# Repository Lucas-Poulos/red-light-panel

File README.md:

# red-light-panel

A battery-powered 660nm red light therapy panel. 4S2P 18650 Li-ion pack
(~74Wh-class), USB-C PD charging, ~74W LED load across two independently
PWM-dimmable channels, STM32-based control with a 4-button HMI.

KiCad 10 hardware project — schematic + BOM. PCB placement/routing is
out of scope for this pass, but the board is fab-ready to route against:
2-layer, 1oz/1oz copper, JLCPCB-standard-service design rules with
margin (not run at the fabrication limit) — see
`docs/pcb_fabrication_rules.md` for the exact values and rationale.
All 153 components are imported onto the board from the schematic.

## Architecture

Seven hierarchical sheets, numbered so KiCad's hierarchy navigator sorts
them in build/reading order:

| Sheet | Description |
|---|---|
| `01_battery_protection` | 4S2P 18650 pack, BQ76920 protection AFE, high-side dual-FET protection, reverse-polarity guard |
| `02_usbc_charging` | USB-C PD input (TPS25751), buck-boost charger (BQ25792), ESD protection |
| `03_power_rail_3v3` | TPS563201 buck regulator, 3.3V system logic rail |
| `04_led_drivers` | 2x LM3409HV PFET-buck constant-current LED driver channels |
| `05_led_array` | 64x Luminus SST-10-DR-B130-K660 660nm LEDs, 2 channels x 8 parallel x 4 series strings |
| `06_mcu_control` | STM32G031K8T6 MCU, SWD debug (Cortex Debug 10-pin + THT breakout), ESD arrays |
| `07_hmi` | 4 tactile buttons (power/dim+/dim-/mode), single-color status LED |

Connectivity uses `GlobalLabel`s throughout rather than wired
hierarchical sheet-symbol pins — see `docs/design_notes.md` for why. The
root sheet (`red-light-panel.kicad_sch`) contains only the 7 sheet
symbols, no components.

## Opening the project

Requires **KiCad 10**. Clone the repo and open `red-light-panel.kicad_pro`
— the project-local `sym-lib-table`/`fp-lib-table` register every stock
library this design uses (via `${KICAD10_SYMBOL_DIR}`/
`${KICAD10_FOOTPRINT_DIR}`, so they resolve on any machine with KiCad 10
installed) plus `libs/red-light-panel.kicad_sym` / `.pretty` for the
handful of parts not in KiCad's stock libraries. No global library setup
is required.

## Regenerating the schematics

The 7 sub-sheets and the root sheet are generated programmatically from
`tools/kicad_gen/` (a small `kiutils`-based builder), not hand-drawn —
see `docs/design_notes.md` "Schematic generation approach" for the full
pipeline and the non-obvious KiCad file-format details it works around.
To rebuild everything from the declarative part lists in
`tools/kicad_gen/sheet*.py`:

```
pip install kiutils sexpdata
python3 tools/kicad_gen/sheet1.py   # ... through sheet7.py
python3 tools/kicad_gen/root_sheet.py
python3 tools/kicad_gen/fix_instance_paths.py
```

## Regenerating the BOM

```
python3 bom/generate_bom.py
```

Wraps `kicad-cli sch export bom` (reads the full hierarchical netlist
including the custom `MPN`/`Manufacturer`/`DigiKey_PN`/`Sheet` fields set
on every symbol) grouped by `(MPN, Value, Footprint)` into
`bom/red-light-panel-bom.csv` — 48 rows, 153 total placed components.

## Current design status

**Verification**: full-hierarchy `kicad-cli sch erc` on
`red-light-panel.kicad_sch` reports **0 errors** (157 cosmetic
"endpoint off grid" warnings from the auto-placed layout, 3 expected
"lib_symbol_mismatch" warnings from stock parts whose KiCad-library
`extends` chain was flattened for pin-position reliability — see
`docs/design_notes.md`). Every one of the 153 placed components has a
linked footprint; zero duplicate reference designators.

### Known open items (flagged, need your review before fab)

**Corrections to the original BOM** (verified real part numbers/topology
fixes, not silent substitutions to different components):
- `TPD4S012DBVR` → **TPD4S012DRYR** (that BVR suffix/package doesn't
  exist for this part; TI only makes it in a 6-pin USON).
- `TPD4E001DZDR` → **TPD4E001DBVR** (same issue; the 4-channel device
  needs a 6-pin SOT-23, not the 4-pin DZD package).
- `TPS25750DRYR` → **TPS25751DREFR** (TPS25750 is TI-marked
  Not-Recommended-for-New-Designs; TPS25751 is the active replacement —
  your decision, see below).
- Fuse `MICROSMD250F/16-2` (originally a placeholder) → **Bel Fuse
  0ZRE0025FF** (0.25A hold current, matching the placeholder's own naming
  convention) — verify hold-current spec against your real current
  budget before finalizing.
- Status LED `APTD1608LSECK/J4-PRV` → confirmed **single-color**
  (`APT1608LSECK/J4-PRV`, no "D") — no real bi-color part exists under
  that family name. Per your decision, D71 (renumbered from D8, see
  below) is now a single-color status LED.
- Reference designators **D6/D7/D8 renumbered to D69/D70/D71**: the
  original BOM's own `D5-D68` (64 LED array elements) numerically
  collided with these three (sheet 6 ESD arrays, sheet 7 status LED).

**Needs your engineering review** (reasonable, documented, but
unverified-against-datasheet or genuinely open decisions):
- **BQ25792's front-end ideal-diode MOSFETs (ACFET/RBFET1/RBFET2) are not
  included** — TI's real reference design needs them on the
  ACDRV1/ACDRV2/BTST1/BTST2 pins, but they weren't itemized in the
  original BOM and weren't invented here unprompted. The charger's
  reverse-blocking front-end is incomplete as generated until you decide
  whether/how to add this.
- **TPS25751DREFR and BQ25792RQMR are hand-built symbols** (no official
  downloadable KiCad source exists for either — confirmed via TI/DigiKey/
  Ultra Librarian). Every pin was sourced from TI's own datasheet pin
  tables, but several individual pins have ambiguous datasheet electrical
  types (TI itself labels some pins as generic "P"/"I/O") — double-check
  before trusting blind, especially: TPS25751's `LDO_1V5`/`DRAIN`/`PPHV`/
  `VBUS_IN`; BQ25792's `BTST1`/`BTST2`/`VAC1`/`VAC2`/`BATP`/`BAT`/`PMID`.
- **TPS25751's power-path topology** (VBUS_IN → internal switch →
  PPHV/DRAIN → BQ25792) is a best-effort interpretation of TI's own
  ambiguous datasheet, not confirmed against a real TI reference design.
- **LED array topology** (8 parallel strings of 4 series LEDs per
  channel, ~625mA/string) is derived from Vf/rail-voltage math, not
  specified by the BOM — verify against the ~74W target power budget and
  the Luminus datasheet's thermal-derating curves.
- **STM32G031 GPIO assignment** (I2C on PB6/PB7, PWM on PA6/PA7, buttons
  on PA0-PA3, NTC ADC on PA4, NRST on PF2) is a reasonable but
  **unverified-against-the-reference-manual** pin choice.
- **Driver inductors** (L2/L3, Vishay IHLP2525CZERR10M01) and the 3.3V
  rail inductor (L1, Wurth 744031220) — values need a real switching-
  frequency calc against LM3409HV's/TPS563201's design equations, not
  just the default values used here.
- **L1's footprint** is a size-matched placeholder (no exact Wurth
  744031220 footprint exists in KiCad's stock libraries).
- **J3's exact GCT USB4105 suffix** (plating/stake length) — defaulted
  to `USB4105-GF-A`; there is no "mount style" suffix (confirmed via
  research — the whole series is one fixed SMT top-mount style).
- **J6's footprint** (generic 2x5 1.27mm SMD header) is electrically
  equivalent to but not the exact Samtec FTSH-105-01-F-DV-K footprint.
- **Calculated component values** flagged inline in their `Value` field
  wherever a real datasheet equation was used instead of an itemized BOM
  value: R3 (3.3V feedback divider bottom leg), R13 (status LED current
  limit), and every "(added, flagged)" support passive (COFF/UVLO
  networks, bootstrap caps, ILIM_HIZ/PROG set resistors, NTC pull-up) —
  see `tools/kicad_gen/sheet*.py` docstrings for the reasoning behind
  each.

None of the above are unresolved *nets* or missing pin connections —
every flagged item is a component-value/part-choice judgment call called
out for your review, consistent with a 0-error ERC pass.

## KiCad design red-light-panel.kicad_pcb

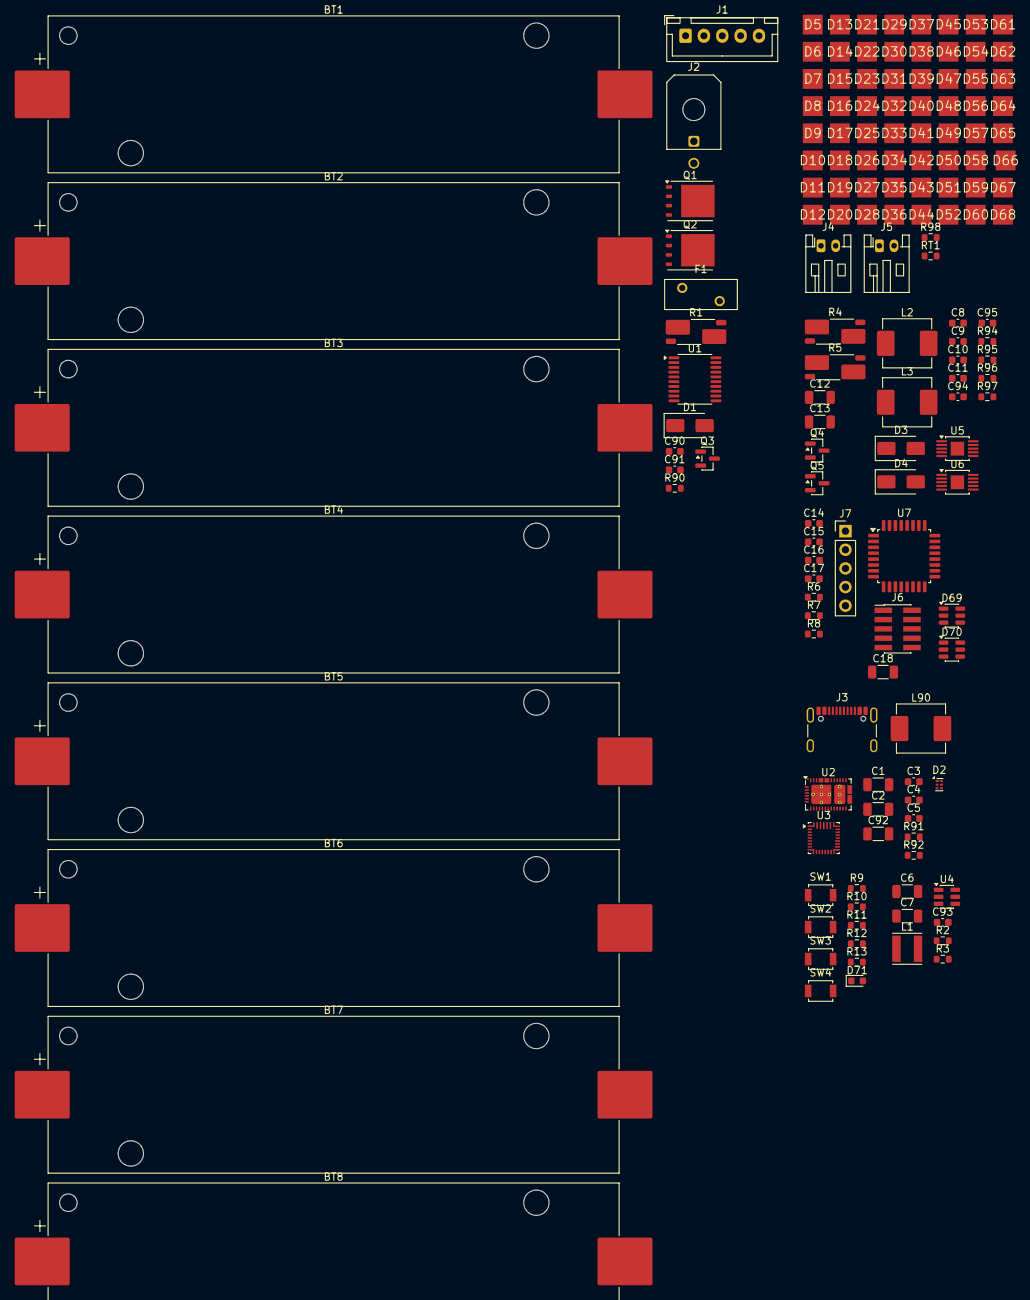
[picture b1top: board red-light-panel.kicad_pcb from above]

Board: 2 copper layers, 153 parts (0 on the bottom side), 98 nets, no tracks yet.

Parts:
BT1, BT2, BT3, BT4, BT5, BT6, BT7, BT8: INR18650-30Q; BatteryHolder_Keystone_1042_1x18650
C1, C2, C6, C7, C12, C13: 10uF; C_1206_3216Metric
C3, C4, C5, C8, C9, C10, C11, C14, C15, C16, C17: 0.1uF; C_0603_1608Metric
C18: 4.7uF; C_1206_3216Metric
C90: 1uF (added, flagged); C_0603_1608Metric
C91: 0.1uF (added, flagged); C_0603_1608Metric
C92: 1uF (added, flagged -- PMID bulk cap per typical 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; C_1206_3216Metric
C93: 2.2nF (added, flagged -- VBST bootstrap cap); C_0603_1608Metric
C94, C95: 100pF (added, flagged -- COFF timing, calc vs L f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; C_0603_1608Metric
D1: SMAJ24CA; D_SMA
D2: TPD4S012DRYR (corrected from BOM's TPD4S012DBVR -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; Texas_USON-6_1x1.45mm_P0.5mm_SMD
D3, D4: SS54; D_SMA
D5, D6, D7, D8, D9, D10, D11, D12, D13, D14, D15, D16, D17, D18, D19, D20, D21, D22, D23, D24, D25, D26, D27, D28, D29, D30, D31, D32, D33, D34, D35, D36, D37, D38, D39, D40, D41, D42, D43, D44, D45, D46, D47, D48, D49, D50, D51, D52, D53, D54, D55, D56, D57, D58, D59, D60, D61, D62, D63, D64, D65, D66, D67, D68: SST-10-DR-B130-K660; LUMINUS_SST-10-3535
D69, D70: TPD4E001DBVR (corrected from BOM's TPD4E001DZDR -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; SOT-23-6
D71: APT1608LSECK/J4-PRV (single-color, corrected per 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; LED_0603_1608Metric
F1: 0.25A resettable; Fuse_BelFuse_0ZRE0025FF_L9.6mm_W3.8mm
J1: JST B5B-XH-A; JST_XH_B5B-XH-A_1x05_P2.50mm_Vertical
J2: Molex 43045-0200; Molex_Micro-Fit_3.0_43045-0200_2x01_P3.00mm_Horizontal
J3: USB4105-GF-A (plating/stake length TBD, flag); USB_C_Receptacle_GCT_USB4105-xx-A_16P_TopMnt_Horizontal
J4, J5: 2-pin screw terminal / JST-PH-2; JST_PH_S2B-PH-K_1x02_P2.00mm_Horizontal
J6: Cortex Debug 10-pin; PinHeader_2x05_P1.27mm_Vertical_SMD
J7: Debug breakout (SWDIO,SWCLK,NRST,3.3V,GND); PinHeader_1x05_P2.54mm_Vertical
L1: 2.2uH (Wurth 744031220); L_Vishay_IFSC-1515AH_4x4x1.8mm
L2, L3: IHLP2525CZERR10M01 (0.10uH); L_Vishay_IHLP-2525
L90: 2.2uH (added, flagged -- calc vs target charge cu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; L_Vishay_IHLP-2525
Q1, Q2: CSD18540Q5B; TDSON-8-1
Q3: AO3401A; SOT-23
Q4, Q5: AO3401A (30V Vds, satisfies brief's margin flag); SOT-23
R1: 0.01R 1%; R_Shunt_Vishay_WSK2512_6332Metric_T2.21mm
R2, R6, R7, R8, R9, R10, R11, R12: 10k; R_0603_1608Metric
R3: 3.01k (calc, flag); R_0603_1608Metric
R4, R5: 0.02R 1%; R_Shunt_Vishay_WSK2512_6332Metric_T2.21mm
R13: 680R (calc vs Vf/If, flag); R_0603_1608Metric
R90: 100k; R_0603_1608Metric
R91: 10k (added, flagged -- ILIM_HIZ set resistor, cal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; R_0603_1608Metric
R92: 4.7k (added, flagged -- PROG set resistor, calc p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; R_0603_1608Metric
R94, R96: 100k (added, flagged -- COFF timing, calc vs L fr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; R_0603_1608Metric
R95, R97: 100k (added, flagged -- UVLO always-on pull-up, n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; R_0603_1608Metric
R98: 10k (added, flagged -- NTC divider pull-up); R_0603_1608Metric
RT1: NCP18XH103F03RB (10k NTC); R_0603_1608Metric
SW1, SW2, SW3, SW4: Omron B3U-1000P; SW_SPST_B3U-1000P
U1: BQ76920PW; TSSOP-20_4.4x6.5mm_P0.65mm
U2: TPS25751DREFR (active replacement for NRND TPS257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; Texas_REF0038A_WQFN-38-2EP_6x4mm_P0.4
U3: BQ25792RQMR; Texas_RQM0029A_VQFN-29_4x4mm_P0.4mm
U4: TPS563201DDCR; SOT-23-6
U5, U6: LM3409HVMY/NOPB; HVSSOP-10-1EP_3x3mm_P0.5mm_EP1.83x1.89mm
U7: STM32G031K8T6; LQFP-32_7x7mm_P0.8mm

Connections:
3V3: C7.1, C14.1, C15.1, C16.1, C17.1, C18.1, D69.6 (VCC), D70.6 (VCC), J6.1 (VTref), J7.4, L1.2, R2.1, R6.1, R7.1, R8.1, R13.1, R98.1, SW1.1, SW2.1, SW3.1, SW4.1, U7.4 (VDD)
BTN_DIMM: D69.4 (IO3), R11.1, SW3.2, U7.9 (PA2)
BTN_DIMP: D69.3 (IO2), R10.1, SW2.2, U7.8 (PA1)
BTN_MODE: D69.5 (IO4), R12.1, SW4.2, U7.10 (PA3)
BTN_PWR: D69.1 (IO1), R9.1, SW1.2, U7.7 (PA0)
D8_A: D71.2 (A), R13.2
FET_MID: Q1.1 (S), Q1.2 (S), Q1.3 (S), Q2.1 (S), Q2.2 (S), Q2.3 (S)
GND: C1.2, C2.2, C3.2, C4.2, C5.2, C6.2, C7.2, C8.2, C9.2, C10.2, C11.2, C14.2, C15.2, C16.2, C17.2, C18.2, C90.2, C91.2, C92.2, C94.2, C95.2, D1.2 (A2), D2.4 (GND), D3.2 (A), D4.2 (A), D69.2 (GND), D70.2 (GND), J3.A1 (GND), J3.A12 (GND), J3.B1 (GND), J3.B12 (GND), J3.SH (SHIELD), J6.3 (GND), J6.5 (GND), J6.9 (GNDDetect), J7.5, R1.2, R3.2, R9.2, R10.2, R11.2, R12.2, R91.2, R92.2, RT1.2, U4.1 (GND), U5.5 (GND), U5.11 (DAP), U6.5 (GND), U6.11 (DAP), U7.5 (VSS)
I2C_SCL: R7.2, U7.30 (PB6)
I2C_SDA: R6.2, U7.31 (PB7)
LED_A+: C12.1, D5.2 (A), D9.2 (A), D13.2 (A), D17.2 (A), D21.2 (A), D25.2 (A), D29.2 (A), D33.2 (A), J4.1, L2.2
LED_A-: C12.2, D8.1 (K), D12.1 (K), D16.1 (K), D20.1 (K), D24.1 (K), D28.1 (K), D32.1 (K), D36.1 (K), J4.2, R4.1, U5.8 (CSP)
LED_A_S0_N0: D5.1 (K), D6.2 (A)
LED_A_S0_N1: D6.1 (K), D7.2 (A)
LED_A_S0_N2: D7.1 (K), D8.2 (A)
LED_A_S1_N0: D9.1 (K), D10.2 (A)
LED_A_S1_N1: D10.1 (K), D11.2 (A)
LED_A_S1_N2: D11.1 (K), D12.2 (A)
LED_A_S2_N0: D13.1 (K), D14.2 (A)
LED_A_S2_N1: D14.1 (K), D15.2 (A)
LED_A_S2_N2: D15.1 (K), D16.2 (A)
LED_A_S3_N0: D17.1 (K), D18.2 (A)
LED_A_S3_N1: D18.1 (K), D19.2 (A)
LED_A_S3_N2: D19.1 (K), D20.2 (A)
LED_A_S4_N0: D21.1 (K), D22.2 (A)
LED_A_S4_N1: D22.1 (K), D23.2 (A)
LED_A_S4_N2: D23.1 (K), D24.2 (A)
LED_A_S5_N0: D25.1 (K), D26.2 (A)
LED_A_S5_N1: D26.1 (K), D27.2 (A)
LED_A_S5_N2: D27.1 (K), D28.2 (A)
LED_A_S6_N0: D29.1 (K), D30.2 (A)
LED_A_S6_N1: D30.1 (K), D31.2 (A)
LED_A_S6_N2: D31.1 (K), D32.2 (A)
LED_A_S7_N0: D33.1 (K), D34.2 (A)
LED_A_S7_N1: D34.1 (K), D35.2 (A)
LED_A_S7_N2: D35.1 (K), D36.2 (A)
LED_B+: C13.1, D37.2 (A), D41.2 (A), D45.2 (A), D49.2 (A), D53.2 (A), D57.2 (A), D61.2 (A), D65.2 (A), J5.1, L3.2
LED_B-: C13.2, D40.1 (K), D44.1 (K), D48.1 (K), D52.1 (K), D56.1 (K), D60.1 (K), D64.1 (K), D68.1 (K), J5.2, R5.1, U6.8 (CSP)
LED_B_S0_N0: D37.1 (K), D38.2 (A)
LED_B_S0_N1: D38.1 (K), D39.2 (A)
LED_B_S0_N2: D39.1 (K), D40.2 (A)
LED_B_S1_N0: D41.1 (K), D42.2 (A)
LED_B_S1_N1: D42.1 (K), D43.2 (A)
LED_B_S1_N2: D43.1 (K), D44.2 (A)
LED_B_S2_N0: D45.1 (K), D46.2 (A)
LED_B_S2_N1: D46.1 (K), D47.2 (A)
LED_B_S2_N2: D47.1 (K), D48.2 (A)
LED_B_S3_N0: D49.1 (K), D50.2 (A)
LED_B_S3_N1: D50.1 (K), D51.2 (A)
LED_B_S3_N2: D51.1 (K), D52.2 (A)
LED_B_S4_N0: D53.1 (K), D54.2 (A)
LED_B_S4_N1: D54.1 (K), D55.2 (A)
LED_B_S4_N2: D55.1 (K), D56.2 (A)
LED_B_S5_N0: D57.1 (K), D58.2 (A)
LED_B_S5_N1: D58.1 (K), D59.2 (A)
LED_B_S5_N2: D59.1 (K), D60.2 (A)
LED_B_S6_N0: D61.1 (K), D62.2 (A)
LED_B_S6_N1: D62.1 (K), D63.2 (A)
LED_B_S6_N2: D63.1 (K), D64.2 (A)
LED_B_S7_N0: D65.1 (K), D66.2 (A)
LED_B_S7_N1: D66.1 (K), D67.2 (A)
LED_B_S7_N2: D67.1 (K), D68.2 (A)
NRST: D70.4 (IO3), J6.10 (~RESET), J7.3, R8.2, U7.6 (PF2)
NTC_SENSE: R98.2, RT1.1, U7.11 (PA4)
unnamed: BT1.1 (+), BT3.2 (-)
unnamed: BT2.1 (+), BT4.2 (-)
unnamed: BT3.1 (+), BT5.2 (-)
unnamed: BT4.1 (+), BT6.2 (-)
unnamed: BT5.1 (+), BT7.2 (-)
unnamed: BT6.1 (+), BT8.2 (-)
PACK_RAW: F1.2, Q3.2 (S)
PACK_RAW_F: F1.1, J2.1
PWM_A: U5.3 (EN), U7.13 (PA6)
PWM_B: U6.3 (EN), U7.14 (PA7)
Q3_GATE: Q3.1 (G), R90.1
STACK_NEG: BT1.2 (-), BT2.2 (-), J1.1, J2.2, R1.1
SWCLK: D70.3 (IO2), J6.4 (SWCLK/TCK), J7.2, U7.25 (PA14)
SWDIO: D70.1 (IO1), J6.2 (SWDIO/TMS), J7.1, U7.24 (PA13)
U4_FB: R2.2, R3.1, U4.4 (VFB)
U4_SW: C93.2, L1.1, U4.2 (SW)
U4_VBST: C93.1, U4.6 (VBST)
U5_COFF: C94.1, R94.2, U5.4 (COFF)
U5_CSN: R4.2, U5.7 (CSN)
U5_PGATE: Q4.1 (G), U5.6 (PGATE)
U5_SW: D3.1 (K), L2.1, Q4.3 (D)
U5_UVLO: R95.2, U5.1 (UVLO)
U5_VCC: C8.1, C9.1, U5.2 (IADJ), U5.9 (VCC)
U6_COFF: C95.1, R96.2, U6.4 (COFF)
U6_CSN: R5.2, U6.7 (CSN)
U6_PGATE: Q5.1 (G), U6.6 (PGATE)
U6_SW: D4.1 (K), L3.1, Q5.3 (D)
U6_UVLO: R97.2, U6.1 (UVLO)
U6_VCC: C10.1, C11.1, U6.2 (IADJ), U6.9 (VCC)
USB_DN: D2.2 (D-), J3.A7 (D-), J3.B7 (D-)
USB_DP: D2.1 (D+), J3.A6 (D+), J3.B6 (D+)
USB_VBUS: C1.1, C2.1, D2.6 (VBUS), J3.A4 (VBUS), J3.A9 (VBUS), J3.B4 (VBUS), J3.B9 (VBUS)
VBAT: BT7.1 (+), BT8.1 (+), C6.1, D1.1 (A1), J1.5, Q1.5 (D), Q3.3 (D), R90.2, U4.3 (VIN), U4.5 (EN)
VBAT_PROT: Q2.5 (D), Q4.2 (S), Q5.2 (S), R94.1, R95.1, R96.1, R97.1, U5.10 (VIN), U6.10 (VIN)

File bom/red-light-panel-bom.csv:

"Reference","Value","MPN","Manufacturer","DigiKey_PN","Qty","Sheet"
"BT1,BT2,BT3,BT4,BT5,BT6,BT7,BT8","INR18650-30Q","Samsung INR18650-30Q","Samsung SDI","INR18650-30Q-B-ND","8","1"
"C1,C2,C6,C12,C13","10uF","CC1206KKX7R8BB106","Yageo","311-4622-1-ND","5","2,3,4"
"C3,C4,C5,C8,C9,C10,C11,C14,C15,C16,C17","0.1uF","CC0603KRX7R9BB104","Yageo","311-1367-1-ND","11","2,4,6"
"C7","10uF","CC1206KKX5R7BB106","Yageo","311-4633-1-ND","1","3"
"C18","4.7uF","CC1206KKX7R8BB475","Yageo","311-4646-1-ND","1","6"
"C90","1uF (added, flagged)","","","","1","1"
"C91","0.1uF (added, flagged)","","","","1","1"
"C92","1uF (added, flagged -- PMID bulk cap per typical app circuit)","","","","1","2"
"C93","2.2nF (added, flagged -- VBST bootstrap cap)","","","","1","3"
"C94,C95","100pF (added, flagged -- COFF timing, calc vs L freq)","","","","2","4"
"D1","SMAJ24CA","SMAJ24CA","Littelfuse","F5351CT-ND","1","1"
"D2","TPD4S012DRYR (corrected from BOM's TPD4S012DBVR -- flag)","TPD4S012DRYR","Texas Instruments","296-TPD4S012DRYRCT-ND","1","2"
"D3,D4","SS54","SS54","onsemi/Diodes Inc (generic SS54)","SS54-E3/57TCT-ND","2","4"
"D5,D6,D7,D8,D9,D10,D11,D12,D13,D14,D15,D16,D17,D18,D19,D20,D21,D22,D23,D24,D25,D26,D27,D28,D29,D30,D31,D32,D33,D34,D35,D36,D37,D38,D39,D40,D41,D42,D43,D44,D45,D46,D47,D48,D49,D50,D51,D52,D53,D54,D55,D56,D57,D58,D59,D60,D61,D62,D63,D64,D65,D66,D67,D68","SST-10-DR-B130-K660","SST-10-DR-B130-K660","Luminus Devices","1462-SST-10-DR-B130-K660-ND (verify exact reel/tape SKU)","64","5"
"D69,D70","TPD4E001DBVR (corrected from BOM's TPD4E001DZDR -- flag)","TPD4E001DBVR","Texas Instruments","296-TPD4E001DBVRCT-ND","2","6"
"D71","APT1608LSECK/J4-PRV (single-color, corrected per your decision)","APT1608LSECK/J4-PRV","Kingbright","754-1552-1-ND","1","7"
"F1","0.25A resettable","0ZRE0025FF (corrected from placeholder MICROSMD250F/16-2 -- FLAG FOR REVIEW)","Bel Fuse","507-1677-1-ND","1","1"
"J1","JST B5B-XH-A","B5B-XH-A","JST","455-1719-ND","1","1"
"J2","Molex 43045-0200","43045-0200","Molex","WM1857-ND","1","1"
"J3","USB4105-GF-A (plating/stake length TBD, flag)","USB4105-GF-A","GCT","GCT USB4105-GF-A-ND (verify exact DigiKey SKU)","1","2"
"J4,J5","2-pin screw terminal / JST-PH-2","B2B-PH-K-S(LF)(SN)","JST","455-1728-ND","2","5"
"J6","Cortex Debug 10-pin","FTSH-105-01-F-DV-K (footprint substituted, flag)","Samtec","SAM8199-ND","1","6"
"J7","Debug breakout (SWDIO,SWCLK,NRST,3.3V,GND)","PREC005SAAN-RC","Sullins","S7036-ND","1","6"
"L1","2.2uH (Wurth 744031220)","744031220","Wurth Elektronik","732-1801-1-ND","1","3"
"L2,L3","IHLP2525CZERR10M01 (0.10uH)","IHLP2525CZERR10M01","Vishay Dale","541-2724-1-ND","2","4"
"L90","2.2uH (added, flagged -- calc vs target charge current)","","","","1","2"
"Q1,Q2","CSD18540Q5B","CSD18540Q5B","Texas Instruments","296-37312-1-ND","2","1"
"Q3","AO3401A","AO3401A","Alpha & Omega Semiconductor","AO3401A-DICT-ND","1","1"
"Q4,Q5","AO3401A (30V Vds, satisfies brief's margin flag)","AO3401A","Alpha & Omega Semiconductor","AO3401A-DICT-ND","2","4"
"R1","0.01R 1%","WSL2512R0100FEA","Vishay Dale","541-2455-1-ND","1","1"
"R2,R6,R7,R8,R9,R10,R11,R12","10k","RC0603FR-0710KL","Yageo","311-10.0KHRCT-ND","8","3,6,7"
"R3","3.01k (calc, flag)","RC0603FR-073K01L","Yageo","311-3.01KHRCT-ND","1","3"
"R4,R5","0.02R 1%","WSL2512R0200FEA","Vishay Dale","541-2456-1-ND","2","4"
"R13","680R (calc vs Vf/If, flag)","RC0603FR-07680RL","Yageo","311-680HRCT-ND","1","7"
"R90","100k","RC0603FR-07100KL","Yageo","311-100KHRCT-ND","1","1"
"R91","10k (added, flagged -- ILIM_HIZ set resistor, calc per datasheet eqn)","","","","1","2"
"R92","4.7k (added, flagged -- PROG set resistor, calc per datasheet eqn)","","","","1","2"
"R94,R96","100k (added, flagged -- COFF timing, calc vs L freq)","","","","2","4"
"R95,R97","100k (added, flagged -- UVLO always-on pull-up, no set threshold)","","","","2","4"
"R98","10k (added, flagged -- NTC divider pull-up)","","","","1","5"
"RT1","NCP18XH103F03RB (10k NTC)","NCP18XH103F03RB","Murata","490-16279-1-ND","1","5"
"SW1,SW2,SW3,SW4","Omron B3U-1000P","B3U-1000P","Omron","SW1020CT-ND","4","7"
"U1","BQ76920PW","BQ7692000PWR","Texas Instruments","296-37299-1-ND","1","1"
"U2","TPS25751DREFR (active replacement for NRND TPS25750DRYR, per your decision)","TPS25751DREFR","Texas Instruments","296-TPS25751DREFR-ND (verify)","1","2"
"U3","BQ25792RQMR","BQ25792RQMR","Texas Instruments","296-BQ25792RQMR-ND (verify)","1","2"
"U4","TPS563201DDCR","TPS563201DDCR","Texas Instruments","296-51654-1-ND","1","3"
"U5,U6","LM3409HVMY/NOPB","LM3409HVMY/NOPB","Texas Instruments","296-30489-1-ND","2","4"
"U7","STM32G031K8T6","STM32G031K8T6","STMicroelectronics","497-STM32G031K8T6TR-ND","1","6"

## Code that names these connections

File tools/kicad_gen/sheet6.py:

"""
Sheet 6 -- MCU & Control.

**GPIO assignment** (not specified by the BOM -- derived and flagged):
STM32G031K8Tx's stock KiCad symbol pin table doesn't literally spell out
"NRST"/"VDDA" as separate names for this 32-pin package (only one VDD/VSS
pair is exposed, and reset shares pin 6 as "PF2" -- ST's own datasheet
names this same physical pin "PF2-NRST" on this package, i.e. GPIO+reset
shared). PA13/PA14 = SWDIO/SWCLK is fixed on every STM32 part (not a
package-specific choice). Everything else below (I2C on PB6/PB7, PWM on
PA6/PA7, buttons on PA0-PA3, NTC ADC on PA4) is a reasonable but
UNVERIFIED-against-the-reference-manual pin choice -- flag for review
against the STM32G031 datasheet's actual alternate-function table before
finalizing firmware/pinout.

- **VDDA bypass (C18)**: this package has no separate VDDA pin in the
  stock symbol (ties internally to VDD) -- C18 is wired to the same
  VDD/GND nets as the other decoupling, as a larger bulk cap for analog
  noise immunity, per the BOM's own description of its purpose.
- **Renumbered D6/D7 -> D69/D70** (FLAG): the original BOM's own ranges
  collide -- D5-D68 (64 LED array elements, sheet 5) numerically includes
  D6, D7, and D8, which the BOM separately assigns to this sheet's ESD
  arrays and sheet 7's status LED. Kept the LED array's documented D5-D68
  range intact (it's the range with an exact count constraint) and moved
  these two out of the way instead.
- **D69** (ESD array, exposed digital lines): wired across the 4 HMI
  button inputs (BTN_PWR/DIMP/DIMM/MODE) -- the lines most exposed to
  user/enclosure-edge ESD.
- **D70** (ESD array, SWD lines/J7 breakout): wired across SWDIO/SWCLK/
  NRST; its 4th channel is left NC (3V3/GND on the J7 breakout don't need
  transient protection the same way signal lines do).
- **STAT_LED_R** does NOT touch this sheet -- per the brief's own net map
  ("Sheet 6 MCU *or* Sheet 2 charger STAT pins -> Sheet 7"), this design
  drives it directly from BQ25792's STAT pin (sheet 2), so no MCU GPIO is
  reserved for it.
"""
import sys, os
sys.path.insert(0, os.path.dirname(os.path.dirname(os.path.abspath(__file__))))
from kicad_gen.builder import build_schematic, add_part, add_pwr_flag, write_and_upgrade, Part

PROJECT = "red-light-panel"
SHEET = "6"


def build():
    sch = build_schematic("MCU & Control", "06_mcu_control")
    embedded = set()

    def P(**kw):
        kw.setdefault("sheet", SHEET)
        return Part(**kw)

    parts = [
        P(ref="U7", lib_file="MCU_ST_STM32G0", entry_name="STM32G031K8Tx", nickname="MCU_ST_STM32G0",
          value="STM32G031K8T6", footprint="Package_QFP:LQFP-32_7x7mm_P0.8mm",
          pins={"1": "NC", "2": "NC", "3": "NC", "4": "3V3", "5": "GND", "6": "NRST",
                "7": "BTN_PWR", "8": "BTN_DIMP", "9": "BTN_DIMM", "10": "BTN_MODE",
                "11": "NTC_SENSE", "12": "NC", "13": "PWM_A", "14": "PWM_B",
                "15": "NC", "16": "NC", "17": "NC", "18": "NC", "19": "NC",
                "20": "NC", "21": "NC", "22": "NC", "23": "NC", "24": "SWDIO",
                "25": "SWCLK", "26": "NC", "27": "NC", "28": "NC", "29": "NC",
                "30": "I2C_SCL", "31": "I2C_SDA", "32": "NC"},
          x=100, y=40, mpn="STM32G031K8T6", manufacturer="STMicroelectronics",
          digikey_pn="497-STM32G031K8T6TR-ND",
          datasheet="https://www.st.com/resource/en/datasheet/stm32g031k8.pdf"),

        P(ref="C14", lib_file="Device", entry_name="C", nickname="Device",
          value="0.1uF", footprint="Capacitor_SMD:C_0603_1608Metric",
          pins={"1": "3V3", "2": "GND"}, x=60, y=20,
          mpn="CC0603KRX7R9BB104", manufacturer="Yageo", digikey_pn="311-1367-1-ND", datasheet=""),
        P(ref="C15", lib_file="Device", entry_name="C", nickname="Device",
          value="0.1uF", footprint="Capacitor_SMD:C_0603_1608Metric",
          pins={"1": "3V3", "2": "GND"}, x=75, y=20,
          mpn="CC0603KRX7R9BB104", manufacturer="Yageo", digikey_pn="311-1367-1-ND", datasheet=""),
        P(ref="C16", lib_file="Device", entry_name="C", nickname="Device",
          value="0.1uF", footprint="Capacitor_SMD:C_0603_1608Metric",
          pins={"1": "3V3", "2": "GND"}, x=90, y=20,
          mpn="CC0603KRX7R9BB104", manufacturer="Yageo", digikey_pn="311-1367-1-ND", datasheet=""),
        P(ref="C17", lib_file="Device", entry_name="C", nickname="Device",
          value="0.1uF", footprint="Capacitor_SMD:C_0603_1608Metric",
          pins={"1": "3V3", "2": "GND"}, x=105, y=20,
          mpn="CC0603KRX7R9BB104", manufacturer="Yageo", digikey_pn="311-1367-1-ND", datasheet=""),
        P(ref="C18", lib_file="Device", entry_name="C", nickname="Device",
          value="4.7uF", footprint="Capacitor_SMD:C_1206_3216Metric",
          pins={"1": "3V3", "2": "GND"}, x=120, y=20,
          mpn="CC1206KKX7R8BB475", manufacturer="Yageo", digikey_pn="311-4646-1-ND", datasheet=""),

        P(ref="R6", lib_file="Device", entry_name="R", nickname="Device",
          value="10k", footprint="Resistor_SMD:R_0603_1608Metric",
          pins={"1": "3V3", "2": "I2C_SDA"}, x=180, y=20,
          mpn="RC0603FR-0710KL", manufacturer="Yageo", digikey_pn="311-10.0KHRCT-ND", datasheet=""),
        P(ref="R7", lib_file="Device", entry_name="R", nickname="Device",
          value="10k", footprint="Resistor_SMD:R_0603_1608Metric",
          pins={"1": "3V3", "2": "I2C_SCL"}, x=195, y=20,
          mpn="RC0603FR-0710KL", manufacturer="Yageo", digikey_pn="311-10.0KHRCT-ND", datasheet=""),
        P(ref="R8", lib_file="Device", entry_name="R", nickname="Device",
          value="10k", footprint="Resistor_SMD:R_0603_1608Metric",
          pins={"1": "3V3", "2": "NRST"}, x=210, y=20,
          mpn="RC0603FR-0710KL", manufacturer="Yageo", digikey_pn="311-10.0KHRCT-ND", datasheet=""),

        P(ref="J6", lib_file="Connector", entry_name="Conn_ARM_JTAG_SWD_10", nickname="Connector",
          value="Cortex Debug 10-pin", footprint="Connector_PinHeader_1.27mm:PinHeader_2x05_P1.27mm_Vertical_SMD",
          pins={"1": "3V3", "2": "SWDIO", "3": "GND", "4": "SWCLK", "5": "GND",
                "6": "NC", "7": "NC", "8": "NC", "9": "GND", "10": "NRST"},
          x=60, y=70, mpn="FTSH-105-01-F-DV-K (footprint substituted, flag)", manufacturer="Samtec",
          digikey_pn="SAM8199-ND", datasheet="https://suddendocs.samtec.com/prints/ftsh-1xx-xx-xxx-dv-x-mkt.pdf"),

        P(ref="J7", lib_file="Connector_Generic", entry_name="Conn_01x05", nickname="Connector_Generic",
          value="Debug breakout (SWDIO,SWCLK,NRST,3.3V,GND)", footprint="Connector_PinHeader_2.54mm:PinHeader_1x05_P2.54mm_Vertical",
          pins={"1": "SWDIO", "2": "SWCLK", "3": "NRST", "4": "3V3", "5": "GND"},
          x=100, y=70, mpn="PREC005SAAN-RC", manufacturer="Sullins", digikey_pn="S7036-ND",
          datasheet="https://www.sullinscorp.com/media/UserFiles/document/PREC005SAAN-RC.pdf"),

        P(ref="D69", lib_file="PROJECT", entry_name="TPD4E001DBVR", nickname="red-light-panel",
          value="TPD4E001DBVR (corrected from BOM's TPD4E001DZDR -- flag)", footprint="Package_TO_SOT_SMD:SOT-23-6",
          pins={"1": "BTN_PWR", "2": "GND", "3": "BTN_DIMP", "4": "BTN_DIMM", "5": "BTN_MODE", "6": "3V3"},
          x=140, y=70, mpn="TPD4E001DBVR", manufacturer="Texas Instruments",
          digikey_pn="296-TPD4E001DBVRCT-ND", datasheet="https://www.ti.com/lit/ds/symlink/tpd4e001.pdf"),

        P(ref="D70", lib_file="PROJECT", entry_name="TPD4E001DBVR", nickname="red-light-panel",
          value="TPD4E001DBVR (corrected from BOM's TPD4E001DZDR -- flag)", footprint="Package_TO_SOT_SMD:SOT-23-6",
          pins={"1": "SWDIO", "2": "GND", "3": "SWCLK", "4": "NRST", "5": "NC", "6": "3V3"},
          x=175, y=70, mpn="TPD4E001DBVR", manufacturer="Texas Instruments",
          digikey_pn="296-TPD4E001DBVRCT-ND", datasheet="https://www.ti.com/lit/ds/symlink/tpd4e001.pdf"),
    ]

    for part in parts:
        add_part(sch, part, PROJECT, embedded)

    # 3V3's one project-wide PWR_FLAG lives on sheet 3, GND's on sheet 1
    # -- not repeated here (multiple PWR_FLAGs on the same merged net
    # conflict with each other once the hierarchy is combined).

    out = "/Users/lucaspoulos/kicad-projects/red-light-panel/06_mcu_control.kicad_sch"
    print(write_and_upgrade(sch, out))


if __name__ == "__main__":
    build()

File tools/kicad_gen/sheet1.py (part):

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    # --- protection AFE ---
    parts.append(P(ref="U1", lib_file="Battery_Management", entry_name="BQ76920PW", nickname="Battery_Management",
                   value="BQ76920PW", footprint="Package_SO:TSSOP-20_4.4x6.5mm_P0.65mm",
                   pins={"1": "DSG_GATE", "2": "CHG_GATE", "3": "GND", "4": "I2C_SDA", "5": "I2C_SCL",
                         "6": "NC", "7": "U1_CAP1", "8": "U1_REGOUT", "9": "VBAT", "10": "VBAT",
                         "11": "NC", "12": "VBAT", "13": "VBAT", "14": "TAP3", "15": "TAP2",
                         "16": "TAP1", "17": "STACK_NEG", "18": "STACK_NEG", "19": "GND", "20": "NC"},
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    # --- protection FETs (high-side, back-to-back) ---
    parts.append(P(ref="Q1", lib_file="Transistor_FET", entry_name="CSD18540Q5B", nickname="Transistor_FET",
                   value="CSD18540Q5B", footprint="Package_TO_SOT_SMD:TDSON-8-1",
                   pins={"1": "FET_MID", "2": "FET_MID", "3": "FET_MID", "4": "DSG_GATE", "5": "VBAT"},
                   x=200, y=20, mpn="CSD18540Q5B", manufacturer="Texas Instruments",
                   digikey_pn="296-37312-1-ND", datasheet="http://www.ti.com/lit/gpn/csd18540q5b"))
    parts.append(P(ref="Q2", lib_file="Transistor_FET", entry_name="CSD18540Q5B", nickname="Transistor_FET",
                   value="CSD18540Q5B", footprint="Package_TO_SOT_SMD:TDSON-8-1",
                   pins={"1": "FET_MID", "2": "FET_MID", "3": "FET_MID", "4": "CHG_GATE", "5": "VBAT_PROT"},
                   x=200, y=45, mpn="CSD18540Q5B", manufacturer="Texas Instruments",
                   digikey_pn="296-37312-1-ND", datasheet="http://www.ti.com/lit/gpn/csd18540q5b"))

    # --- reverse-polarity ideal diode ---
    parts.append(P(ref="Q3", lib_file="Transistor_FET", entry_name="AO3401A", nickname="Transistor_FET",
                   value="AO3401A", footprint="Package_TO_SOT_SMD:SOT-23",
                   pins={"1": "Q3_GATE", "2": "PACK_RAW", "3": "VBAT"},
                   x=90, y=90, mpn="AO3401A", manufacturer="Alpha & Omega Semiconductor",
                   digikey_pn="AO3401A-DICT-ND", datasheet="http://www.aosmd.com/pdfs/datasheet/AO3401A.pdf"))
    parts.append(P(ref="R90", lib_file="Device", entry_name="R", nickname="Device",
                   value="100k", footprint="Resistor_SMD:R_0603_1608Metric",
                   pins={"1": "Q3_GATE", "2": "VBAT"}, x=110, y=90,
                   mpn="RC0603FR-07100KL", manufacturer="Yageo", digikey_pn="311-100KHRCT-ND",
                   datasheet=""))

    # --- current sense ---
    parts.append(P(ref="R1", lib_file="Device", entry_name="R", nickname="Device",
                   value="0.01R 1%", footprint="Resistor_SMD:R_Shunt_Vishay_WSK2512_6332Metric_T2.21mm",
                   pins={"1": "STACK_NEG", "2": "GND"}, x=140, y=100,
                   mpn="WSL2512R0100FEA", manufacturer="Vishay Dale", digikey_pn="541-2455-1-ND",
                   datasheet="https://www.vishay.com/docs/30112/wsl.pdf"))

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                   datasheet="https://www.littelfuse.com/media?resourcetype=datasheets&itemid=75e32973-b177-4ee3-a0ff-cedaf1abdb93&filename=smaj-datasheet"))
    parts.append(P(ref="F1", lib_file="Device", entry_name="Fuse", nickname="Device",
                   value="0.25A resettable", footprint="Fuse:Fuse_BelFuse_0ZRE0025FF_L9.6mm_W3.8mm",
                   pins={"1": "PACK_RAW_F", "2": "PACK_RAW"}, x=60, y=90,
                   mpn="0ZRE0025FF (corrected from placeholder MICROSMD250F/16-2 -- FLAG FOR REVIEW)",
                   manufacturer="Bel Fuse", digikey_pn="507-1677-1-ND",
                   datasheet="https://www.belfuse.com/resources/datasheets/circuitprotection/ds-cp-0zre-series.pdf"))
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    # --- connectors ---
    parts.append(P(ref="J1", lib_file="Connector_Generic", entry_name="Conn_01x05", nickname="Connector_Generic",
                   value="JST B5B-XH-A", footprint="Connector_JST:JST_XH_B5B-XH-A_1x05_P2.50mm_Vertical",
                   pins={"1": "STACK_NEG", "2": "TAP1", "3": "TAP2", "4": "TAP3", "5": "VBAT"},
                   x=140, y=20, mpn="B5B-XH-A", manufacturer="JST", digikey_pn="455-1719-ND",
                   datasheet="https://www.jst-mfg.com/product/pdf/eng/eXH.pdf"))
    parts.append(P(ref="J2", lib_file="Connector_Generic", entry_name="Conn_01x02", nickname="Connector_Generic",
                   value="Molex 43045-0200", footprint="Connector_Molex:Molex_Micro-Fit_3.0_43045-0200_2x01_P3.00mm_Horizontal",
                   pins={"1": "PACK_RAW_F", "2": "STACK_NEG"}, x=20, y=90,
                   mpn="43045-0200", manufacturer="Molex", digikey_pn="WM1857-ND",
                   datasheet="https://www.molex.com/pdm_docs/sd/430450200_sd.pdf"))

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
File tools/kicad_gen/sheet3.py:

"""
Sheet 3 -- 3.3V Logic Rail.

- EN tied directly to VBAT (always-enabled -- TPS563201 has an internal
  EN pull-up per datasheet, direct tie is a standard simplification).
- VFB divider: R2 (10k, per BOM's RC0603FR-0710KL) on top (3V3->FB), R3
  (3.01k, calculated) on bottom (FB->GND). TPS563201 Vref = 0.768V typ.
  per datasheet -> R3 = R2 * Vref/(Vout-Vref) = 10k * 0.768/(3.3-0.768)
  = ~3.03k, rounded to the nearest E96 value (3.01k). FLAG FOR REVIEW --
  double check against the exact datasheet Vref spec/tolerance before fab.
- C93 (added, flagged): VBST-to-SW bootstrap cap, required by the
  datasheet's typical application circuit for the high-side driver, not
  itemized as a separate BOM row. Typical value 2.2nF-10nF; using 2.2nF.
- L1 footprint: no exact Wurth 744031220 footprint exists in KiCad's
  stock libraries. Using a similarly-sized placeholder
  (Vishay IFSC-1515AH, 4x4mm vs. WE-TPC 4828's ~4.8x4.8mm) -- FLAG FOR
  REVIEW, build/source the real footprint before fab. Matches the
  brief's own pre-existing "confirm inductor value vs datasheet calc"
  open item.
"""
import sys, os
sys.path.insert(0, os.path.dirname(os.path.dirname(os.path.abspath(__file__))))
from kicad_gen.builder import build_schematic, add_part, add_pwr_flag, write_and_upgrade, Part

PROJECT = "red-light-panel"
SHEET = "3"


def build():
    sch = build_schematic("3.3V Logic Rail", "03_power_rail_3v3")
    embedded = set()

    def P(**kw):
        kw.setdefault("sheet", SHEET)
        return Part(**kw)

    parts = [
        P(ref="U4", lib_file="Regulator_Switching", entry_name="TPS563201", nickname="Regulator_Switching",
          value="TPS563201DDCR", footprint="Package_TO_SOT_SMD:SOT-23-6",
          pins={"1": "GND", "2": "U4_SW", "3": "VBAT", "4": "U4_FB", "5": "VBAT", "6": "U4_VBST"},
          x=100, y=20, mpn="TPS563201DDCR", manufacturer="Texas Instruments",
          digikey_pn="296-51654-1-ND", datasheet="https://www.ti.com/lit/ds/symlink/tps563201.pdf"),

        P(ref="L1", lib_file="Device", entry_name="L", nickname="Device",
          value="2.2uH (Wurth 744031220)", footprint="Inductor_SMD:L_Vishay_IFSC-1515AH_4x4x1.8mm",
          pins={"1": "U4_SW", "2": "3V3"}, x=130, y=20,
          mpn="744031220", manufacturer="Wurth Elektronik", digikey_pn="732-1801-1-ND",
          datasheet="https://www.we-online.com/components/products/datasheet/744031220.pdf"),

        P(ref="C6", lib_file="Device", entry_name="C", nickname="Device",
          value="10uF", footprint="Capacitor_SMD:C_1206_3216Metric",
          pins={"1": "VBAT", "2": "GND"}, x=80, y=45,
          mpn="CC1206KKX7R8BB106", manufacturer="Yageo", digikey_pn="311-4622-1-ND", datasheet=""),

        P(ref="C7", lib_file="Device", entry_name="C", nickname="Device",
          value="10uF", footprint="Capacitor_SMD:C_1206_3216Metric",
          pins={"1": "3V3", "2": "GND"}, x=150, y=45,
          mpn="CC1206KKX5R7BB106", manufacturer="Yageo", digikey_pn="311-4633-1-ND", datasheet=""),

        P(ref="R2", lib_file="Device", entry_name="R", nickname="Device",
          value="10k", footprint="Resistor_SMD:R_0603_1608Metric",
          pins={"1": "3V3", "2": "U4_FB"}, x=170, y=20,
          mpn="RC0603FR-0710KL", manufacturer="Yageo", digikey_pn="311-10.0KHRCT-ND", datasheet=""),

        P(ref="R3", lib_file="Device", entry_name="R", nickname="Device",
          value="3.01k (calc, flag)", footprint="Resistor_SMD:R_0603_1608Metric",
          pins={"1": "U4_FB", "2": "GND"}, x=170, y=45,
          mpn="RC0603FR-073K01L", manufacturer="Yageo", digikey_pn="311-3.01KHRCT-ND", datasheet=""),

        P(ref="C93", lib_file="Device", entry_name="C", nickname="Device",
          value="2.2nF (added, flagged -- VBST bootstrap cap)", footprint="Capacitor_SMD:C_0603_1608Metric",
          pins={"1": "U4_VBST", "2": "U4_SW"}, x=115, y=45,
          mpn="", manufacturer="", digikey_pn="", datasheet=""),
    ]

    for part in parts:
        add_part(sch, part, PROJECT, embedded)

    # TPS563201's SW pin is type "output", not "power_out" -- so despite
    # feeding 3V3 through L1, there's no genuine power_out pin on this net
    # anywhere in the project. 3V3 gets its one PWR_FLAG here (where the
    # rail originates). VBAT is not flagged: BQ25792's BAT pin (power_out,
    # sheet 2) is a genuine driver for it project-wide. GND's one
    # project-wide PWR_FLAG lives on sheet 1 (see docs/design_notes.md --
    # multiple PWR_FLAGs on the same merged net conflict with each other).
    add_pwr_flag(sch, "3V3", 80, 60, embedded, flag_id="3")

    out = "/Users/lucaspoulos/kicad-projects/red-light-panel/03_power_rail_3v3.kicad_sch"
    print(write_and_upgrade(sch, out))


if __name__ == "__main__":
    build()

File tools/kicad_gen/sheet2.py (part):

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    parts.append(P(ref="J3", lib_file="Connector", entry_name="USB_C_Receptacle_USB2.0_16P", nickname="Connector",
                   value="USB4105-GF-A (plating/stake length TBD, flag)",
                   footprint="Connector_USB:USB_C_Receptacle_GCT_USB4105-xx-A_16P_TopMnt_Horizontal",
                   pins={"A1": "GND", "A4": "USB_VBUS", "A5": "CC1", "A6": "USB_DP", "A7": "USB_DN",
                         "A8": "NC", "A9": "USB_VBUS", "A12": "GND", "B1": "GND", "B4": "USB_VBUS",
                         "B5": "CC2", "B6": "USB_DP", "B7": "USB_DN", "B8": "NC", "B9": "USB_VBUS",
                         "B12": "GND", "SH": "GND"},
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    parts.append(P(ref="D2", lib_file="PROJECT", project_symbol="TPD4S012DRYR", entry_name="TPD4S012DRYR", nickname="red-light-panel",
                   value="TPD4S012DRYR (corrected from BOM's TPD4S012DBVR -- flag)",
                   footprint="Package_SON:Texas_USON-6_1x1.45mm_P0.5mm_SMD",
                   pins={"1": "USB_DP", "2": "USB_DN", "3": "NC", "4": "GND", "5": "NC", "6": "USB_VBUS"},
                   x=60, y=20, mpn="TPD4S012DRYR", manufacturer="Texas Instruments",
                   digikey_pn="296-TPD4S012DRYRCT-ND", datasheet="https://www.ti.com/lit/ds/symlink/tpd4s012.pdf"))

    parts.append(P(ref="C1", lib_file="Device", entry_name="C", nickname="Device",
                   value="10uF", footprint="Capacitor_SMD:C_1206_3216Metric",
                   pins={"1": "USB_VBUS", "2": "GND"}, x=20, y=45,
                   mpn="CC1206KKX7R8BB106", manufacturer="Yageo", digikey_pn="311-4622-1-ND", datasheet=""))
    parts.append(P(ref="C2", lib_file="Device", entry_name="C", nickname="Device",
                   value="10uF", footprint="Capacitor_SMD:C_1206_3216Metric",
                   pins={"1": "USB_VBUS", "2": "GND"}, x=35, y=45,
                   mpn="CC1206KKX7R8BB106", manufacturer="Yageo", digikey_pn="311-4622-1-ND", datasheet=""))

    # --- U2 TPS25751DREFR: PD sink controller + integrated power path switch ---
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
